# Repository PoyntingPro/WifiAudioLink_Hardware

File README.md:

# WiFiAudioLink

by: *Anirudh Madhusudhan, Emmanuel Gerald Ndour*

**Faculty of Technology and Bionics**

***Rhine-Waal University of Applied Sciences***

Date: 12.01.2024

## Abstract

With a dash of DIY (Do It Yourself) spirit and a sprinkle of ingenuity, we embarked on a mission: to bridge the gap between our vintage audio companions and the vast world of the internet. With this project, we developped a pcb that enables the transformation of wired Speakers and even headhones into wireless ones. We can listen to our music or podcast through our phones or computers with bluetooth on devices that initially couldn't do it. To do this we used the technology of the ESP32 microcontroller. It became our secret weapon, breathing new life into our faithful old speakers. The magic happened on a custom-made PCB, where wires, circuits and programming wove a symphony of connectivity.

This project isn't just about wires and circuits, though. It's about preserving the soul of these speakers, letting them dance to the beat of the digital age. It proves that innovation doesn't require a hefty budget but just creativity and a dash of determination. It also protects the environment as we will be less tempted to throw away our old wired speakers that we might consider as outdated. We want to share this journey with you, in the hopes that it sparks a fire in others to embark on their own adventures in tech transformation.

So, welcome to our world of resurrected speakers, where the past meets the future, and where old melodies find new life. Together, let's turn forgotten relics into vibrant voices in the modern chorus of life.

Table of Contents
=================

* [WiFiAudioLink](#wifiaudiolink)
   * [Abstract](#abstract)
   * [Table of Contents](#table-of-contents)
   * [1  Introduction](#1--introduction)
      * [1.1 Background:](#11-background)
      * [1.2 Presentation of chapters:](#12-presentation-of-chapters)
   * [2 Bill Of Materials](#2-bill-of-materials)
   * [3 Theory:](#3-theory)
   * [4  Schematic design and additional visuals:](#4--schematic-design-and-additional-visuals)
      * [4.1 Schematic design:](#41-schematic-design)
      * [4.2 Additional Visuals:](#42-additional-visuals)
   * [5 Power Requirements:](#5-power-requirements)
   * [6 Hardware and Software Description](#6-hardware-and-software-description)
      * [6.1 Hardware description:](#61-hardware-description)
      * [6.1.1 ESP32-WROOM-32E:](#611-esp32-wroom-32e)
      * [6.1.2 LM1084IT-3.3 Voltage regulator:](#612-lm1084it-33-voltage-regulator)
      * [6.1.3 Audio Jack Connector:](#613-audio-jack-connector)
      * [6.1.4 OLED Screen:](#614-oled-screen)
      * [6.1.5 PCB as Capacitor:](#615-pcb-as-capacitor)
      * [6.2 Software descripton:](#62-software-descripton)
   * [7 Assembly Process:](#7-assembly-process)
   * [8 Testing](#8-testing)
   * [9 Challenges:](#9-challenges)
      * [10 Results](#10-results)
      * [11 Discussion](#11-discussion)
   * [12 Improvements and future upgrades:](#12-improvements-and-future-upgrades)
   * [13	Concluding Comments](#13concluding-comments)
   * [14 References](#14-references)

## 1  Introduction
### 1.1 Background:
As students our pockets don't run deep, and the siren call of those sleek, internet-connected speakers feels like a distant dream. So, what's the solution? We turn to what we have: a collection of old, cherished speakers that have seen better days. They might not be the shiniest or the latest, but they hold a special place in our hearts. That's the reason why we decided to make this PCB.

### 1.2 Presentation of chapters:
In our report, we systematically outline the progression from the initial project concept to its actual implementation. Chapter 2 provides an overview of the primary components incorporated into our Printed Circuit Board (PCB). Subsequently, Chapter 3 delves into the interconnections among these components. The schematic design is detailed in Chapter 4, while Chapter 5 is dedicated to the computation of power requirements. In Chapter 6, both hardware and software implementations are thoroughly described. Following this, Chapter 7 elucidates the assembly process of the PCB. The subsequent chapter is dedicated to the testing procedures conducted on the PCB. Chapter 9 addresses the challenges encountered during the project, and Chapter 10 offers a presentation of the results. We discussed those results in chapter 11. Future improvements and potential upgrades are explored in Chapter 12. Concluding remarks and references are respectively covered in Chapters 13 and 14. This structured approach allows for a comprehensive exploration of each phase in the development and realization of the project.

## 2 Bill Of Materials

We used the following components during our project
|Components|Quantity|Price in euros|
|---------|--------|-------|
|ESP32-WROOM-32E| 1 | 2.67 |
|Audio Jack Connector| 1 | 1.49 |
|10 Microfarad Capacitor| 1 | 0.75 |
|150 Microfarad Capacitor| 1 | 0.80 |
|LM1084IT-3.3 voltage regulator| 1 | 2.63 |
|OLED Screen| 1 | 7.79 |
|Red LED| 1 | 0.09 |
|Switch | 2 | 0.71 |
|DC Barrel Power Connector| 1 | 1.20 | 

## 3 Theory:
The wireless speaker conversion PCB is carefully crafted to seamlessly integrate various components for optimal functionality. At the heart of the design lies the ESP32-WROOM-32E, a powerful and versatile microcontroller that serves as the core processing unit. A voltage regulator ensures stable power supply to the system, maintaining consistent performance. The inclusion of a power jack connector facilitates easy power input, while an audio jack connector seamlessly interfaces with the wired speaker. Two capacitors are strategically placed for smoothing and filtering purposes, contributing to improved signal integrity. The integration of an OLED screen provides a user-friendly interface for monitoring and configuring the wireless speaker system. To indicate the operational status, a red LED is incorporated, visually signaling when the PCB is powered.

## 4  Schematic design and additional visuals:

### 4.1 Schematic design:

### 4.2 Additional Visuals: 

## 5 Power Requirements:

1. ESP-32: 
```math
P_{esp} = 3.3V \cdot 379mA = 1.25W
```
> the current 379mA is directly from the datasheet as the peak current when using the Wifi RF module at 19.5 dBm

2. Low dropout voltage regulator: 
```math
P_{reg} = (V_{in} - V_{out}) \cdot I_{L} 
```
> The power supply we are using is running at 6V but any power supply above 3.5V should work to power the circuit. Low the input voltage lower the power requirement
```math
P_{reg} = (6V - 3.3V) \cdot 379mA 
```
```math
{P_{reg} = 1.02W}
```
**Total Power Requirement**
```math
P_{total} = P_{esp} + P_{reg} = 1.25W + 1.02W 
\\

```
```math
P_{total} = 2.27W
```

## 6 Hardware and Software Description

### 6.1 Hardware description:

### 6.1.1 ESP32-WROOM-32E:
The ESP32-WROOM-32E is a highly integrated and powerful Wi-Fi and Bluetooth dual-mode module based on the ESP32 chip. This compact module features a dual-core Xtensa LX6 microprocessor, running at up to 240MHz, with abundant memory resources including 520KB of internal SRAM and 4MB of flash memory. It supports 802.11 b/g/n Wi-Fi and Bluetooth 4.2 connectivity, making it suitable for a wide range of IoT applications. The module also includes a rich set of peripheral interfaces, such as SPI, I2C, UART, PWM, and GPIO, providing flexibility for various sensor and peripheral connections. With its low power consumption and advanced features, the ESP32-WROOM-32E is well-suited for applications requiring wireless communication and efficient processing in a compact form factor.

### 6.1.2 LM1084IT-3.3 Voltage regulator:
The LM1084IT-3.3 is a low dropout voltage regulator designed for providing a stable output voltage of 3.3 volts with a maximum dropout voltage of 1.5 volts. This linear regulator is part of the LM1084 series and features a TO-220 package for efficient heat dissipation. With a maximum output current of 5 amps, it is capable of powering a variety of electronic devices. The LM1084IT-3.3 incorporates thermal shutdown and current limit protection mechanisms to enhance reliability. It operates over a wide input voltage range and maintains a high level of accuracy and regulation, making it suitable for applications where a stable and precise 3.3-volt power supply is required, such as in embedded systems, microcontrollers, and other electronic circuits.

### 6.1.3 Audio Jack Connector:
The audio jack connector is a standardized hardware interface widely used for transmitting analog audio signals between electronic devices. Typically found in audio equipment such as headphones, speakers, and mobile devices, the connector consists of a 3.5mm or 1/8-inch cylindrical plug with a metal tip, ring, and sleeve configuration. The tip carries the left audio channel, the ring often carries the right audio channel, and the sleeve is the common ground. The connector may also support additional features like microphone input. Audio jacks provide a simple and reliable method for connecting audio devices, allowing for the seamless playback of audio content across various platforms and devices, making them a ubiquitous component in consumer electronics.

### 6.1.4 OLED Screen:
The OLED (Organic Light Emitting Diode) screen is a display technology that utilizes organic compounds to emit light when an electric current is applied. OLED screens are characterized by their self-emitting pixels, allowing for high contrast ratios, vibrant colors, and faster response times compared to traditional display technologies. The screen typically consists of multiple layers, including a substrate, organic layers, and a transparent electrode. OLEDs are known for their flexibility, enabling the creation of curved or flexible displays. They are widely used in various electronic devices, including smartphones, televisions, and wearables, due to their ability to deliver crisp images with deep blacks and energy efficiency. Additionally, OLED screens can be manufactured in different sizes, making them suitable for diverse applications and form factors.

### 6.1.5 PCB as Capacitor:
We tried to use the two layers of copper of the PCB separated by a isolation layer to use as a DC-blocking capacitor. Using the dimenstion of the final PCB, we later on added a capacitor to the schematic.

**Theoretical Capacitance**

```math

C = \frac{\epsilon_r \epsilon_oA}{d}
=>
C = \frac{4.7 \cdot  8.85 \cdot 10^{-12} Fm^{-1} \cdot 43.18mm \cdot 77.47mm }{1.6mm}

\\
C = 87.2pF
```

**Measured Capacitance**

```math

C = 8pF
```

### 6.2 Software descripton:

**Bluetooth Class**

```cpp:

class BluetoothA2DPCommon {
    public:
        /// Destructor
        virtual ~BluetoothA2DPCommon() = default;
    
        /// activate / deactivate the automatic reconnection to the last address (per default this is on)
        void set_auto_reconnect(bool active);

        /// Closes the connection
        virtual void disconnect();

        /// Reconnects to the last device
        virtual bool reconnect();

        /// Connnects to the indicated address
        virtual bool connect_to(esp_bd_addr_t peer);

        /// Calls disconnect or reconnect
        virtual void set_connected(bool active);

        /// Closes the connection and stops A2DP
        virtual void end(bool releaseMemory=false);

        /// Checks if A2DP is connected
        virtual  bool is_connected() = 0;

        /// Sets the volume (range 0 - 255)
        virtual void set_volume(uint8_t volume){
            ESP_LOGI(BT_AV_TAG, "set_volume: %d", volume);
            volume_value = volume;
            volume_control()->set_volume(volume);
            volume_control()->set_enabled(true);
            is_volume_used = true;
        }
            
        /// Determines the actual volume
        virtual int get_volume(){
            return is_volume_used ? volume_value : 0;
        }

        /// you can define a custom VolumeControl implementation
        virtual void set_volume_control(A2DPVolumeControl *ptr){
            volume_control_ptr = ptr;
        }

        /// Determine the actual audio state
        virtual esp_a2d_audio_state_t get_audio_state();
    
        /// Determine the connection state
        virtual esp_a2d_connection_state_t get_connection_state();

        /// Set the callback that is called when the connection state is changed
        /// This callback is called before the I2S bus is changed.
        virtual void set_on_connection_state_changed(void (*callBack)(esp_a2d_connection_state_t state, void *), void *obj=nullptr);

        /// Set the callback that is called after the audio state has changed.
        /// This callback is called after the I2S bus has changed.
        virtual void set_on_audio_state_changed_post(void (*callBack)(esp_a2d_audio_state_t state, void*), void* obj=nullptr);

        /// Set the callback that is called when the audio state is changed
        virtual void set_on_audio_state_changed(void (*callBack)(esp_a2d_audio_state_t state, void*), void* obj=nullptr);

       /// Prevents that the same method is executed multiple times within the indicated time limit
        virtual void debounce(void(*cb)(void),int ms);

        /// Logs the free heap
        void log_free_heap();

        /// converts esp_a2d_connection_state_t to a string
        const char* to_str(esp_a2d_connection_state_t state);

        /// converts a esp_a2d_audio_state_t to a string
        const char* to_str(esp_a2d_audio_state_t state);

        /// converts a esp_bd_addr_t to a string - the string is 18 characters long! 
        const char* to_str(esp_bd_addr_t bda);

#if ESP_IDF_VERSION >= ESP_IDF_VERSION_VAL(4, 0, 0)
        /// converts esp_avrc_playback_stat_t to a string
        const char* to_str(esp_avrc_playback_stat_t state);
#endif

        /// defines the task priority (the default value is configMAX_PRIORITIES - 10)
        void set_task_priority(UBaseType_t priority){
            task_priority = priority;
        }

        /// Defines the core which is used to start the tasks (to process the events and audio queue)
        void set_task_core(BaseType_t core){
            task_core = core;
        }

        /// Defines the queue size of the event task 
        void set_event_queue_size(int size){
            event_queue_size = size;
        }

        /// Defines the stack size of the event task (in bytes)
        void set_event_stack_size(int size){
            event_stack_size = size;
        }

        /// Provides the address of the last device
        virtual esp_bd_addr_t* get_last_peer_address() {
            return &last_connection;
        }

#if ESP_IDF_VERSION >= ESP_IDF_VERSION_VAL(4, 0, 0)
    /// Bluetooth discoverability
    virtual void set_discoverability(esp_bt_discovery_mode_t d);
#endif

    /// Bluetooth connectable
    virtual void set_connectable(bool connectable) {
        set_scan_mode_connectable(connectable);
    }

    /// Provides the actual SSID name
    virtual const char* get_name() {
        return bt_name;
    }

    /// clean last connection (delete)
    virtual void clean_last_connection();

    protected:
        const char* bt_name = {0};
        esp_bd_addr_t peer_bd_addr;
        ReconnectStatus reconnect_status = NoReconnect;
        unsigned long reconnect_timout=0;
        unsigned int default_reconnect_timout=10000;
        bool is_autoreconnect_allowed = false; 
        uint32_t debounce_ms = 0;
        A2DPDefaultVolumeControl default_volume_control;
        A2DPVolumeControl *volume_control_ptr = nullptr;
        esp_bd_addr_t last_connection = {0,0,0,0,0,0};
        bool is_start_disabled = false;
        void (*connection_state_callback)(esp_a2d_connection_state_t state, void* obj) = nullptr;
        void (*audio_state_callback)(esp_a2d_audio_state_t state, void* obj) = nullptr;
        void (*audio_state_callback_post)(esp_a2d_audio_state_t state, void* obj) = nullptr;
        void *connection_state_obj = nullptr;
        void *audio_state_obj = nullptr;
        void *audio_state_obj_post = nullptr;
        const char *m_a2d_conn_state_str[4] = {"Disconnected", "Connecting", "Connected", "Disconnecting"};
        const char *m_a2d_audio_state_str[3] = {"Suspended", "Stopped", "Started"};
        const char *m_avrc_playback_state_str[5] = {"stopped", "playing", "paused", "forward seek", "reverse seek"};
        esp_a2d_audio_state_t audio_state = ESP_A2D_AUDIO_STATE_STOPPED;
        esp_a2d_connection_state_t connection_state = ESP_A2D_CONNECTION_STATE_DISCONNECTED;
        UBaseType_t task_priority = configMAX_PRIORITIES - 10;
        // volume 
        uint8_t volume_value = 0;
        bool is_volume_used = false;
        BaseType_t task_core = 1;

        int event_queue_size = 20;
        int event_stack_size = 3072;

#if ESP_IDF_VERSION >= ESP_IDF_VERSION_VAL(4, 0, 0)
        esp_bt_discovery_mode_t discoverability = ESP_BT_GENERAL_DISCOVERABLE;
#endif

        virtual esp_err_t esp_a2d_connect(esp_bd_addr_t peer) = 0;
        virtual const char* last_bda_nvs_name() = 0;
        virtual void get_last_connection();
        virtual void set_last_connection(esp_bd_addr_t bda);
        virtual bool has_last_connection();
        // change the scan mode
        virtual void set_scan_mode_connectable(bool connectable);
        virtual void set_scan_mode_connectable_default() = 0;

        /// provides access to the VolumeControl object
        virtual A2DPVolumeControl* volume_control() {
            return volume_control_ptr !=nullptr ? volume_control_ptr : &default_volume_control;
        }
};
```

**I2S configuration structure**

```cpp:

static const i2s_config_t i2s_config = {
    .mode = (i2s_mode_t) (I2S_MODE_MASTER | I2S_MODE_TX | I2S_MODE_DAC_BUILT_IN),
    .sample_rate = 44100, // corrected by info from bluetooth
    .bits_per_sample = (i2s_bits_per_sample_t) 16, /* the DAC module will only take the 8bits from MSB */
    .channel_format = I2S_CHANNEL_FMT_RIGHT_LEFT,
    .communication_format = (i2s_comm_format_t)I2S_COMM_FORMAT_STAND_MSB,
    .intr_alloc_flags = 0, // default interrupt priority
    .dma_buf_count = 8,
    .dma_buf_len = 64,
    .use_apll = false
};

```

## 7 Assembly Process:
In order to complete our project, the opportunity was given to us in the lab to use several machines and tools. We will list them and explain how they helped us achieve our goals.

-**Solder Paste Stencil**:
The primary function of the solder paste stencil is to facilitate the precise application of solder paste onto the pads of a PCB.
We carefully used the solder paste before the placement of the SMD components. After using the Solder Paste Stencil, we now had to place the SMD components with the help of the Pick and Place machine.

-**Pick and Place machine**:
This machine helped us place our SMD components. The machine is organized in such a way that we can pick the SMD components. Different kinds of SMD components were already available. The machine sucks up the components and with the help of the screen we can place the SMD components with high precision. Despite the machine successfully picking up most of the components, it was impossible for it to pick our ESP32-WROOM-32E. This was a big challenge for us as we were left with two options: Either place the ESP with our hand on the solder paste or solder it with Soldering Iron. We choosed the first option but not without any problem as our hands were moving a lot and we failed several times to placed it at the right place. At each failed attempt to place it, we had to clean the solder paste and try again. After placing the components, it was now time to solder them.

-**Soldering Reflow Oven**:
The Soldering Reflow Oven was a crucial tool in our surface mount design assembly. It followed a precise temperature profile which involved multiple stages. Preheat: Gradually raising the temperature to remove any residual solvents from the solder paste. Soak: Holding the temperature at a specific level to allow the solder paste to fully liquefy and wet the component leads and PCB pads. Reflow: Rapidly heating to the peak temperature, causing the solder to melt and form the solder joints. Cooling: Gradually lowering the temperature to solidify the solder joints. The Soldering Reflow Oven has a screen that showed us the temperature and the time left. With this machine, we successfully soldered the SMD components. However all our components were not SMD ones as we also had some through hole components to solder and to do it we used the soldering iron.

-**Soldering Iron**: 
A soldering iron is a handheld tool with a metal tip that heats up for the purpose of melting solder, a metal alloy with a low melting point. The primary function of the soldering iron was to solder electronic components on a printed circuit board (PCB). We used it to solder our voltage regulator, our capacitor, our audio jack connector and the Power Jack/Connector.

## 8 Testing
Once all components were soldered onto the PCB for the wireless speaker conversion, a meticulous testing process was initiated to ensure the integrity of the connections and the overall functionality of the device. The first step involved a thorough examination using a multimeter, focusing on both ground and power connections. This comprehensive check aimed to identify any potential shorts or irregularities that could compromise the performance of the wireless speaker system. Following the multimeter tests, an oscilloscope was employed to delve deeper into the electrical characteristics. Specifically, the oscilloscope was used to inspect waveforms and calculate noise levels, crucial considerations given the nature of audio processing. This step was essential to gauge the extent of any unwanted electrical interference or noise within the system, ensuring that the converted wireless speakers would deliver clear and high-quality audio output. The oscilloscope's precision allowed for a detailed analysis of the electrical signals, enabling the identification and rectification of any anomalies before finalizing the wireless transformation of the speakers.

## 9 Challenges:
It is important to point the fact that we didn't get our PCB working at the first try. Our success was preceded by some challenges and disappointments. In our first try we printed and etched the PCB in the lab. However the two sides of our PCB weren't perfectly aligned and the cooper started disappearing. This could have resulted in the PCB not achieving it's purpose. 

We therefore decided to order the PCB to avoid the two problems we were faced. We soldered the components on the ordered PCB and tested it. Again, we didn't get the expected results. Our PCB was partly working because the volume was too low as the amplifier didn't fullfill it's purpose. While trying to desolder our ESP32 microcontroller, we unfortunately broke it. Another issue was that our PCB was unnecessarily too big and we could make it way smaller.

We came up with new ideas and the goal to reduce the size of our PCB and good news this time it work perfectly. 

### 10 Results

### 11 Discussion
We designed a new circuit. The biggest difference to the previous ones is the removal of the audio amplifier and also the efficient use of the space because our final PCB is 76% smaller than the previous version. We once again ordered the PCB and after its arrival, we started soldering again (YES! Aafter so many tries we're now experts at soldering). Once the assembly process was done, we started programming the microcontroller. We tested our PCB with headphones and Speakers. The hard work payed off and our project was fully functional. We were of course happy and proud to have succeeded a project that many people qualified as too ambitious or too complicated. 

## 12 Improvements and future upgrades:
In our continuous pursuit of enhancing the functionality and aesthetics of our wireless speaker conversion PCB, we envision several exciting future upgrades. First on the list is the integration of voice control capabilities, leveraging advanced technologies to enable users to effortlessly command and manipulate the speakers through vocal commands. This addition will bring a new dimension of user convenience and hands-free operation to our wireless speaker system. Additionally, we plan to incorporate a dedicated volume control feature, allowing users to easily adjust audio levels to suit their preferences. This enhancement aims to offer a more personalized and immersive audio experience. To complement the upgraded functionalities, we are also planning to design a stylish and durable housing for the PCB, ensuring not only optimal performance but also an appealing visual presence. This aesthetically pleasing enclosure will not only protect the internal components but also contribute to a polished and sophisticated final product. These forward-looking improvements will elevate our wireless speaker conversion PCB, providing users with a seamless, feature-rich, and visually pleasing audio solution.

## 13	Concluding Comments
This project had a significant importance for us as it gave us have a deeper understanding of the electronics world but we hope it will help in the effort of saving the environment as people will now think about recycling their old speakers or headphones. With this project we felt like real engineers from the research and development to the production. We saw the real applications of voltage regulators, capacitors and microcontrollers. We also gained insight about project management. 
The feedbacks we got from the tutors Jure and Thomas, Mr. Kremer, Mr. Muhs and Professor Hartanto helped us in the continuous improvement of the project. 
After long discussion we made the decision to start serial production of the PCB as many people are interested. We also want to make it cheap, as we estimated the total cost to be around 10 euros and we target the populations that can't afford to buy wireless speakers.

## 14 References

* [1] DroneBot Workshop. (2022, May 22). _ESP32 SOUND - WORKING WITH I2S_. Youtube. https://www.youtube.com/watch?v=m-MPBjScNRk
* [2] GreatScott. (2020, July 12). _Building a Digital Music Player with I2S?! What is I2S!_ . Youtube. https://www.youtube.com/watch?v=qNLvoSQCx60 
* [3] Texas instruments, "LM1084 5-A Low Dropout Positive Regulators", LM1084 datasheet, Sept. 1999 [Revised Jan. 2015]. https://www.ti.com/lit/ds/symlink/lm1084.pdf?ts=1705070693008&ref_url=https%253A%252F%252Fwww.google.com%252F
* [4] Espressif Systems, " esp32-wroom-32e datasheet ", Jan. 2023. https://www.espressif.com/sites/default/files/documentation/esp32-wroom-32e_esp32-wroom-32ue_datasheet_en.pdf 
* [5] Cspot, https://github.com/feelfreelinux/cspot

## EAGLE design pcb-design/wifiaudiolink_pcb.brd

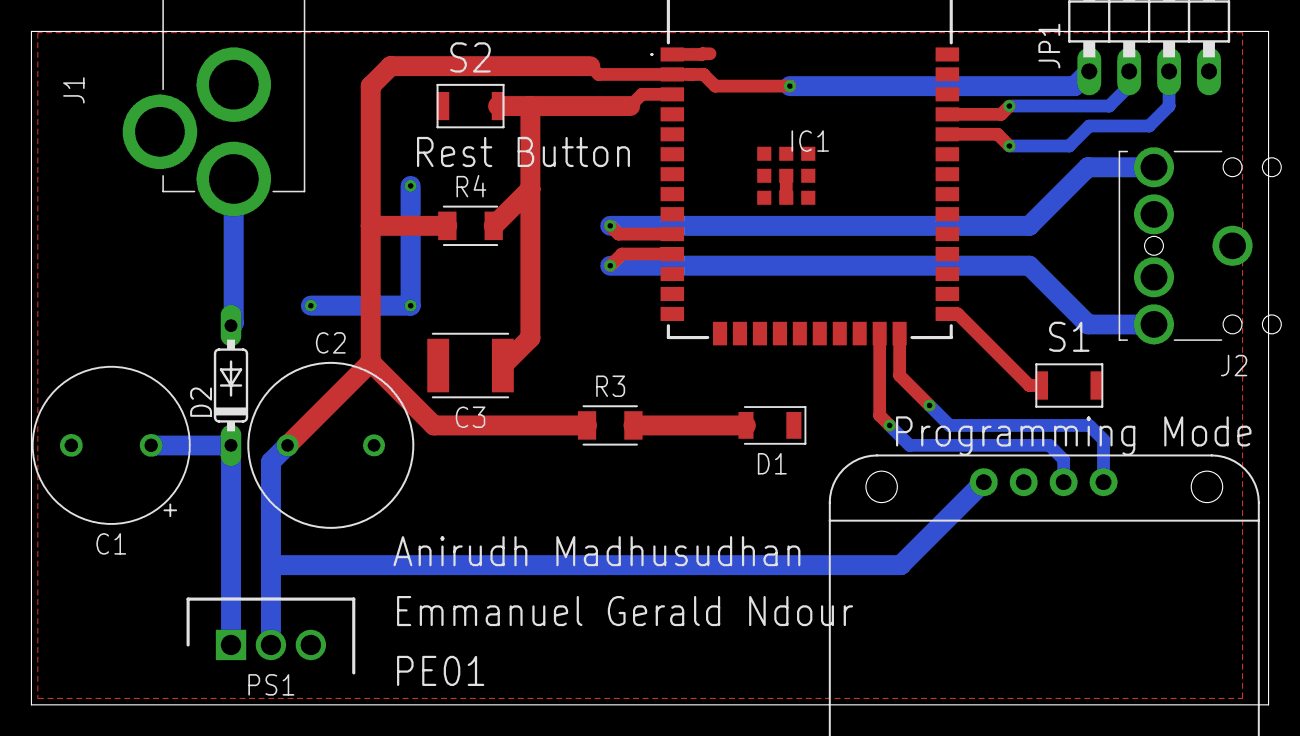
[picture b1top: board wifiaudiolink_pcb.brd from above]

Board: 2 copper layers, 78.7 x 42.9 mm, 15 parts (0 on the bottom side), 13 nets.

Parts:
C1: 10µF; CAPPRD508W65D1000H1100B
C2: 150µF; CAPRD550W60D1025H1250B
C3: 0.1µF; CAPC4532X135
D1: LED_RED; LEDC3216X75N_FLAT-R
D2: 1N4148DO35-7; DO35-7
IC1: ESP32-WROOM-32E-N8; ESP32WROOM32EN8
J1: PRT-00119; PRT00119
J2: SJ1-3523N; SJ13523N
JP1: PINHD-1X4/90; 1X04/90
PS1: LM1084IT-3.3_NOPB; TO254P470X1028X1955-3P
R3: 10; RESC3216X70
R4: 10k; RESC3216X70
S1, S2: B3U-1000P(M)
U$1: OLED_0.96_I2C

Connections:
GND: C1.2, C2.2, C3.2, D1.C, IC1.1, IC1.38, IC1.39, IC1.40, IC1.41, IC1.42, IC1.43, IC1.44, IC1.45, IC1.46, IC1.47, J1.2, J1.3, J2.1, JP1.4, PS1.3, S1.2, S2.1, U$1.GND
LEFT: IC1.10, J2.2
unnamed: IC1.25, S1.1
unnamed: C3.1, IC1.3, R4.2, S2.2
unnamed: IC1.34, JP1.3
unnamed: IC1.35, JP1.2
unnamed: D1.A, R3.2
unnamed: D2.A, J1.1
RIGHT: IC1.11, J2.3
SCL: IC1.23, U$1.SCL
SDA: IC1.24, U$1.SDA
VDD33: C2.1, IC1.2, JP1.1, PS1.2, R3.1, R4.1, U$1.VCC
V_SUPPLY: C1.1, D2.C, PS1.1

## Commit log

2024-01-13 Final Files
2024-01-13 Added Code files
2025-09-13 Update README with external image and formatting
